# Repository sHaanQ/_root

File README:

╔╗ ┌─┐┌─┐┬┌─
╠╩╗│ ││ │├┴┐
╚═╝└─┘└─┘┴ ┴

Local Store

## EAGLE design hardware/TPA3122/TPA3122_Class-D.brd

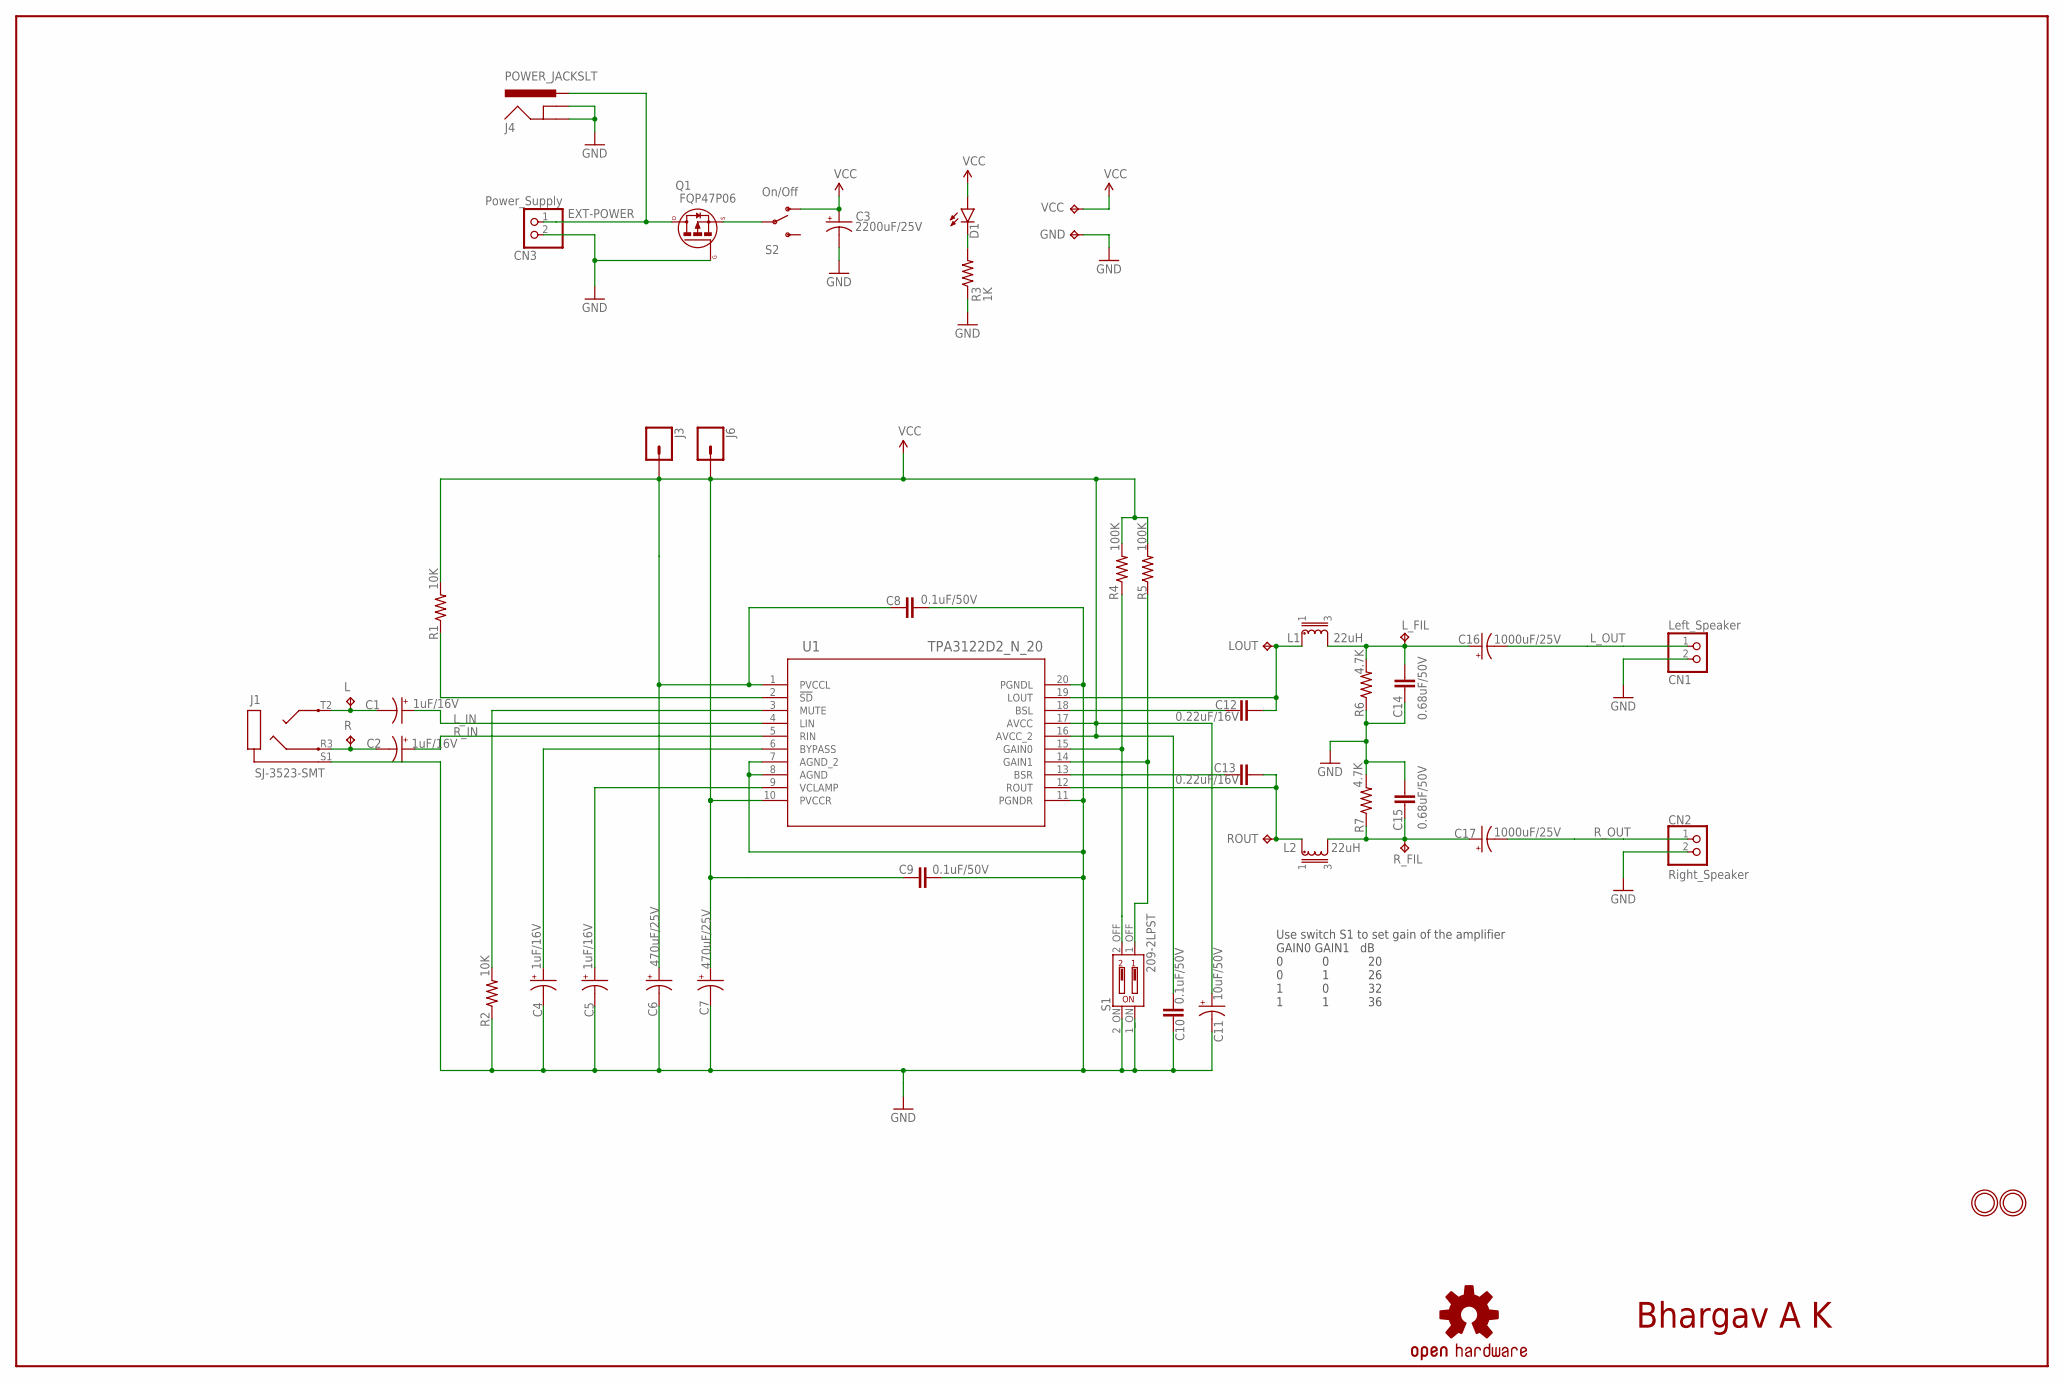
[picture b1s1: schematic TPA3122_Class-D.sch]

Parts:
C1, C2, C4, C5: 1uF/16V; E2,5-5
C3: 2200uF/25V; E5-13
C6, C7: 470uF/25V; E5-10,5
C8, C9, C10: 0.1uF/50V; C050-024X044
C11: 10uF/50V; E2,5-5
C12, C13: 0.22uF/16V; C050-024X044
C14, C15: 0.68uF/50V; C050-024X044
C16, C17: 1000uF/25V; E5-10,5
CN1: Left_Speaker; JST-PH-2-THM
CN2: Right_Speaker; JST-PH-2-THM
CN3: Power_Supply; JST-PH-2-THM
D1: LED3MM; LED_3MM
GND: TPB2,54; B2,54
J1: SJ-3523-SMT
J3, J6: CONN_01; 1X01
J4: POWER_JACKSLT; POWER_JACK_SLOT
L: TPB2,54; B2,54
L1, L2: 22uH; MURATA_1200RS
LOGO1: OSHW-LOGOM; OSHW-LOGO-M
LOUT: TPB2,54; B2,54
L_FIL: TPB2,54; B2,54
Q1: FQP47P06; TO220
R: TPB2,54; B2,54
R1, R2: 10K; 0309/10
R3: 1K; 0309/10
R4, R5: 100K; 0309/10
R6, R7: 4.7K; 0309/10
ROUT: TPB2,54; B2,54
R_FIL: TPB2,54; B2,54
S1: 209-2LPST
S2: SWITCH-SPDTPTH; SWITCH-SPDT
U1: TPA3122D2_N_20; N20
U$2, U$3: MOUNTINGHOLE2.5_THICK; MOUNTINGHOLE_2.5_PLATED_THICK
VCC: TPB2,54; B2,54

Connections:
BSL: C12.1, U1.18 (BSL)
BSR: C13.1, U1.13 (BSR)
BYPASS: C4.+, U1.6 (BYPASS)
EXT-POWER: CN3.1 (1_VCC), J4.PWR, Q1.D
GAIN0: R4.1, S1.2_OFF, U1.15 (GAIN0)
GAIN1: R5.1, S1.1_OFF, U1.14 (GAIN1)
GND: C3.-, C4.-, C5.-, C6.-, C7.-, C8.2, C9.2, C10.2, C11.-, C14.2, C15.1, CN1.2 (2_GND), CN2.2 (2_GND), CN3.2 (2_GND), GND.TP, J1.S1, J4.GND@1 (GNDBREAK), J4.GND@2 (GND), Q1.G, R2.1, R3.1, R6.1, R7.2, S1.1_ON, S1.2_ON, U1.7 (AGND_2), U1.8 (AGND), U1.11 (PGNDR), U1.20 (PGNDL)
LED_K: D1.K (C), R3.2
LEFT: C1.-, J1.T2, L.TP
LOUT: C12.2, L1.1, LOUT.TP, U1.19 (LOUT)
L_FILTERED: C14.1, C16.+, L1.3, L_FIL.TP, R6.2
L_IN: C1.+, U1.4 (LIN)
L_OUT: C16.-, CN1.1 (1_VCC)
MUTE: R2.2, U1.3 (MUTE)
PMOS_VOLTAGE_SRC: Q1.S, S2.2
RIGHT: C2.-, J1.R3, R.TP
ROUT: C13.2, L2.1, ROUT.TP, U1.12 (ROUT)
R_FILTERED: C15.2, C17.+, L2.3, R7.1, R_FIL.TP
R_IN: C2.+, U1.5 (RIN)
R_OUT: C17.-, CN2.1 (1_VCC)
SD: R1.1, U1.2 (!SD)
VCC: C3.+, C6.+, C7.+, C8.1, C9.1, C10.1, C11.+, D1.A, J3.1, J6.1, R1.2, R4.2, R5.2, S2.1 (O), U1.1 (PVCCL), U1.10 (PVCCR), U1.16 (AVCC_2), U1.17 (AVCC), VCC.TP
VCLAMP: C5.+, U1.9 (VCLAMP)

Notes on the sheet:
On/Off
Bhargav A K
Use switch S1 to set gain of the amplifier GAIN0 GAIN1 dB 0 0 20 0 1 26 1 0 32 1 1 36

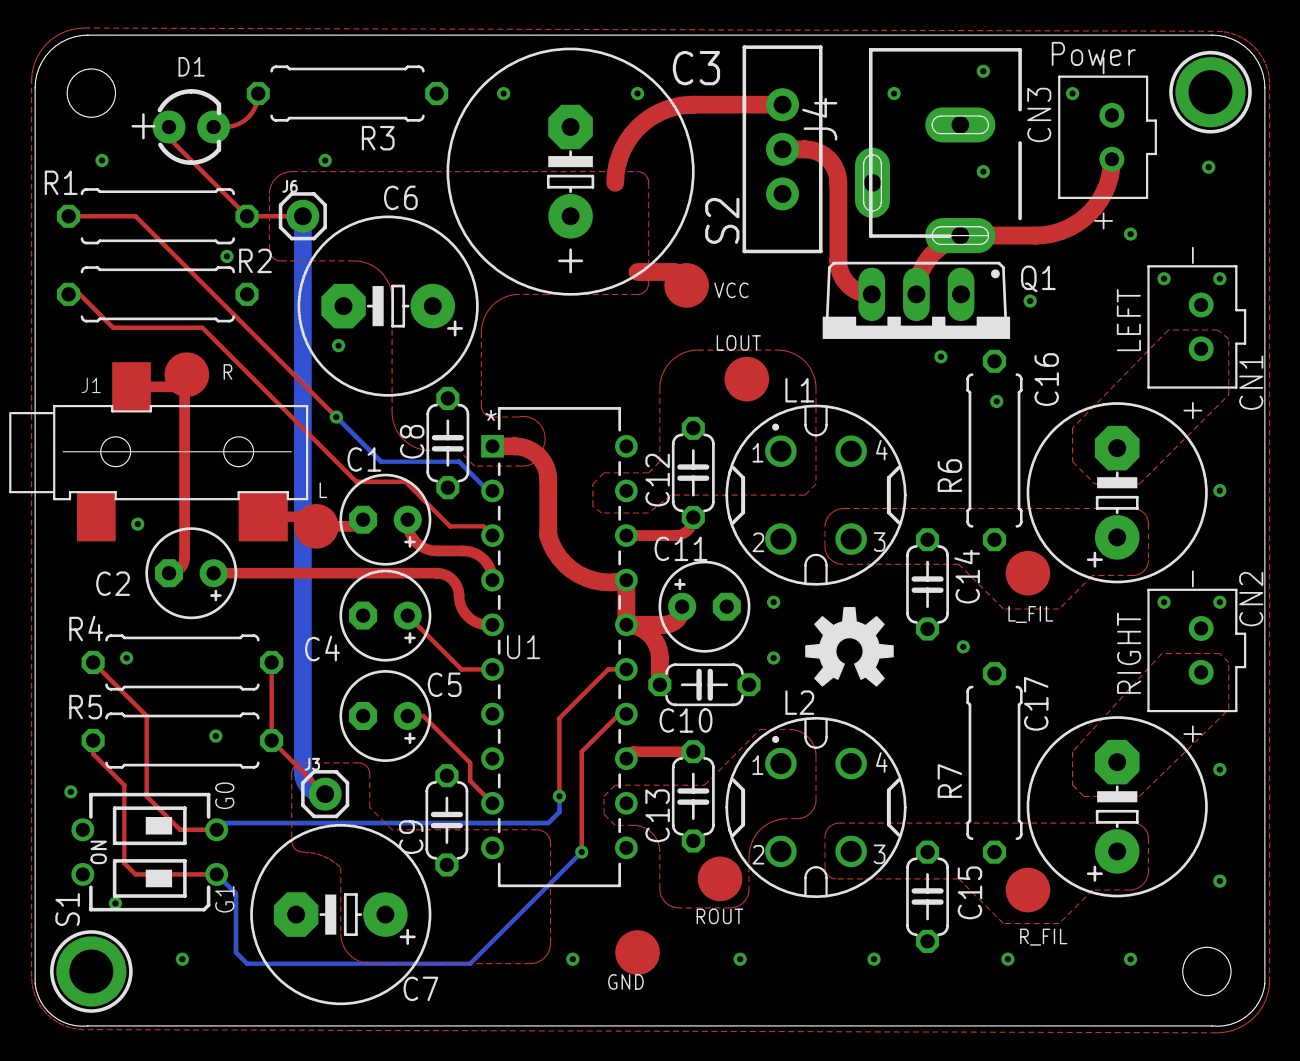
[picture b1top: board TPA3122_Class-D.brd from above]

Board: 2 copper layers, 70.0 x 56.4 mm, 49 parts (0 on the bottom side), 23 nets.

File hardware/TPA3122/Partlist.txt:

Partlist

Exported from TPA3122_Class-D.sch at 25/01/18 9:06 PM

EAGLE Version 8.4.0 Copyright (c) 1988-2017 Autodesk, Inc.

Assembly variant: 

Part     Value          Device          Package         Library                    Sheet

C1       1uF/16V        CPOL-USE2.5-5   E2,5-5          rcl                        1
C2       1uF/16V        CPOL-USE2.5-5   E2,5-5          rcl                        1
C3       2200uF/25V     CPOL-USE5-13    E5-13           rcl                        1
C4       1uF/16V        CPOL-USE2.5-5   E2,5-5          rcl                        1
C5       1uF/16V        CPOL-USE2.5-5   E2,5-5          rcl                        1
C6       470uF/25V      CPOL-USE5-10.5  E5-10,5         rcl                        1
C7       470uF/25V      CPOL-USE5-10.5  E5-10,5         rcl                        1
C8       0.1uF/50V      C-EU050-024X044 C050-024X044    rcl                        1
C9       0.1uF/50V      C-EU050-024X044 C050-024X044    rcl                        1
C10      0.1uF/50V      C-EU050-024X044 C050-024X044    rcl                        1
C11      10uF/50V       CPOL-USE2.5-5   E2,5-5          rcl                        1
C12      0.22uF/16V     C-EU050-024X044 C050-024X044    rcl                        1
C13      0.22uF/16V     C-EU050-024X044 C050-024X044    rcl                        1
C14      0.68uF/50V     C-EU050-024X044 C050-024X044    rcl                        1
C15      0.68uF/50V     C-EU050-024X044 C050-024X044    rcl                        1
C16      1000uF/25V     CPOL-USE5-10.5  E5-10,5         rcl                        1
C17      1000uF/25V     CPOL-USE5-10.5  E5-10,5         rcl                        1
CN1      Left_Speaker   JST_2PIN-THM    JST-PH-2-THM    TPA3122                    1
CN2      Right_Speaker  JST_2PIN-THM    JST-PH-2-THM    TPA3122                    1
CN3      Power_Supply   JST_2PIN-THM    JST-PH-2-THM    TPA3122                    1
D1                      LED3MM          LED_3MM         SparkFun-LED               1
GND      TPB2,54        TPB2,54         B2,54           tlv                        1
J1       SJ-3523-SMT    SJ-3523-SMT     SJ-3523-SMT     TLV                        1
J3                      CONN_01         1X01            SparkFun-Connectors        1
J4       POWER_JACKSLT  POWER_JACKSLT   POWER_JACK_SLOT SparkFun-Connectors        1
J6                      CONN_01         1X01            SparkFun-Connectors        1
L        TPB2,54        TPB2,54         B2,54           tlv                        1
L1       22uH           MURATA_1200RS   MURATA_1200RS   TPA3122                    1
L2       22uH           MURATA_1200RS   MURATA_1200RS   TPA3122                    1
LOUT     TPB2,54        TPB2,54         B2,54           tlv                        1
L_FIL    TPB2,54        TPB2,54         B2,54           tlv                        1
Q1       FQP47P06       FQP47P06        TO220           TPA3122                    1
R        TPB2,54        TPB2,54         B2,54           tlv                        1
R1       10K            R-US_0309/10    0309/10         rcl                        1
R2       10K            R-US_0309/10    0309/10         rcl                        1
R3       1K             R-US_0309/10    0309/10         rcl                        1
R4       100K           R-US_0309/10    0309/10         rcl                        1
R5       100K           R-US_0309/10    0309/10         rcl                        1
R6       4.7K           R-US_0309/10    0309/10         rcl                        1
R7       4.7K           R-US_0309/10    0309/10         rcl                        1
ROUT     TPB2,54        TPB2,54         B2,54           tlv                        1
R_FIL    TPB2,54        TPB2,54         B2,54           tlv                        1
S1       209-2LPST      209-2LPST       209-2LPST       TPA3122                    1
S2                      SWITCH-SPDTPTH  SWITCH-SPDT     SparkFun-Electromechanical 1
U1       TPA3122D2_N_20 TPA3122D2_N_20  N20             TPA3122                    1
VCC      TPB2,54        TPB2,54         B2,54           tlv                        1

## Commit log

2015-06-26 Let me set some ground rules
2015-06-26 build setup instructions
2015-07-09 Data-manual
2015-07-11 updates to build
2015-07-11 renaming the file
2015-07-11 Clearing all files
2015-07-11 Initializing a clean repository
2015-07-11 Changes to ground rules
2015-07-11 base64_encoding support
2015-07-12 Length and error check added
2015-07-12 BAUD rate description
2015-07-12 Removing un-necessary files
2015-07-12 Cleaning up sources
2015-07-12 Clean up and modification
2015-07-12 Modifications and cleanup
2015-09-02 Detailed lessons
2015-09-02 Re-arranging a few documents
2015-09-02 Renaming documents
2015-10-01 Board Revision 2.x specific documents
2015-10-04 Re-organizing code and projects
2015-10-04 LED blinky generic
2015-10-04 EDITs
2015-10-04 LED blinky generic, corrected a typo
2015-10-05 Messing with the names
2015-10-05 The light sensor & blinky
2015-10-16 Fixing file names
2015-10-18 Adding a few more documents
2015-11-03 Clean ups and edits
2015-11-03 Make way for the cheatsheet
2015-12-05 Renamed a directory
2016-01-22 Update cmd_cheatsheet
2016-02-19 Renamed python directory
2016-02-19 Re-arranging files
2016-02-19 Adding cheatsheets
2016-02-19 Adding python sheet
2016-02-19 Updated python sheet
2016-02-22 Adding arduino experiments
2016-02-22 Updated a few files
2016-02-22 Updating names
2016-03-04 Renamed directory
2016-03-14 All lower case directories only
2016-03-14 Start porting code to support Raspberry Pi 2
2016-03-16 Updated blinky readme
2016-04-18 Adding information
2016-04-24 Rsync command
2016-08-31 New scripts, files & organizatio of files.
2016-09-10 [Scripts] - Added kernel cleanup script
    Helper script to clean up old installed kernel on my ubuntu machine
2016-09-10 [Scripts][README] - Updated README
2016-09-10 [Scripts][Fix] - Fixed bug in kernel-cleanup script
2016-09-10 [Cleanup][Scripts] - Code cleanup
2016-11-22 [Updates] : Python and Sed commands
2016-12-05 [Record][Speakers] - Record what's being played on your speakers
    Setup
    -----
    1. Run ./install.sh
    2. Go to Dash Home, search for speaker recorder and start recording
    [Works on any Debian based distro]
2016-12-05 [Update] - README
2017-01-07 Updated python cheeatsheet
2017-01-14 Updated files
2017-02-03 Update python_cheatsheet,py
2017-02-11 Updated python_cheatsheet.py
2017-02-19 [Speaker][Recorder] - Fixed broken application and paths
2017-02-23 Rearranging directories and files
2017-03-02 Adding README
2017-03-14 Rename lits-sort-by-index.py to list-sort-by-index.py
2017-04-10 ALSA device driver files
2017-04-12 Rename VNC_systemd.txt to README
2017-04-20 Updated cmd_cheatsheet
2017-04-20 I2S analysis documents
2017-04-22 I2S analysis documents' updates
2017-04-27 Scripts in sidekick
2017-04-27 Updated rpi3 builder with error logging and some level of robustness :\
2017-05-09 Vimrc and Bashrc files
2017-06-01 Update vimrc
2017-09-14 Added images
2017-10-22 Update bashrc
2017-11-01 Moved Aliases to bash_aliases
2017-11-04 I2S Documentation
2017-11-05 Updated I2S Readme
2017-11-09 Updated RPi Readme
2017-11-09 Updated scripts/md
2017-11-12 Update bash_aliases
2017-12-28 Updated README and Added Getting Started PDF
2018-01-06 Adding my Audio codec hardware design
2018-01-25 [TPA3122 Class D Amplifier] - A class D amplifier powered by a DC adapter or bench supply which can deliver an output of upto 15W/channel.
    [Documentation] - H/W documents added.
    [Clock] - 4 Seven Segment Displays (1" Digit Height)
2018-01-27 [TPA3122] - Updates
2018-02-08 Fixed GND mistake in Barrel Jack
2018-03-20 Removed TLV designs
2018-04-15 Changes to Class D Amp
2018-04-15 Corrected TPA3122 Power Jack
2018-05-15 Added Milling layer to Gerber files
2018-05-15 Added Readme with Images
2018-06-07 Speaker Recorder Images
2018-07-03 Zsh changes
2018-07-27 Update zshrc
2018-08-17 Script changes
2018-08-17 New py file - Subprocess Realtime output
2018-08-19 Corrections to Deepspeech Builder
2018-09-05 Changes to Deepspeech builder

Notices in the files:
parts and their libraries:
SparkFun-LED: Licensing: Creative Commons ShareAlike 4.0 International - https://creativecommons.org/licenses/by-sa/4.0
SparkFun-Aesthetics: Licensing: CC v3.0 Share-Alike You are welcome to use this library for commercial purposes.
